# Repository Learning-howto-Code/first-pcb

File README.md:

# first-pcb
I created this project in order to learn how to use Kicad and how the procces works. Hopefully in the future I can create more complicated designs. By the way the github file upload got a little messed up. If there are duplciates of any file, please look at the most recent one, thanks(I'm used to using hte CLI, but didn't want to screw anything up). Also the banner for on blueprint is outdated, but I forgot to chagne it. Sorry

## 3D view

## Schematic 

## Cart Screenshot

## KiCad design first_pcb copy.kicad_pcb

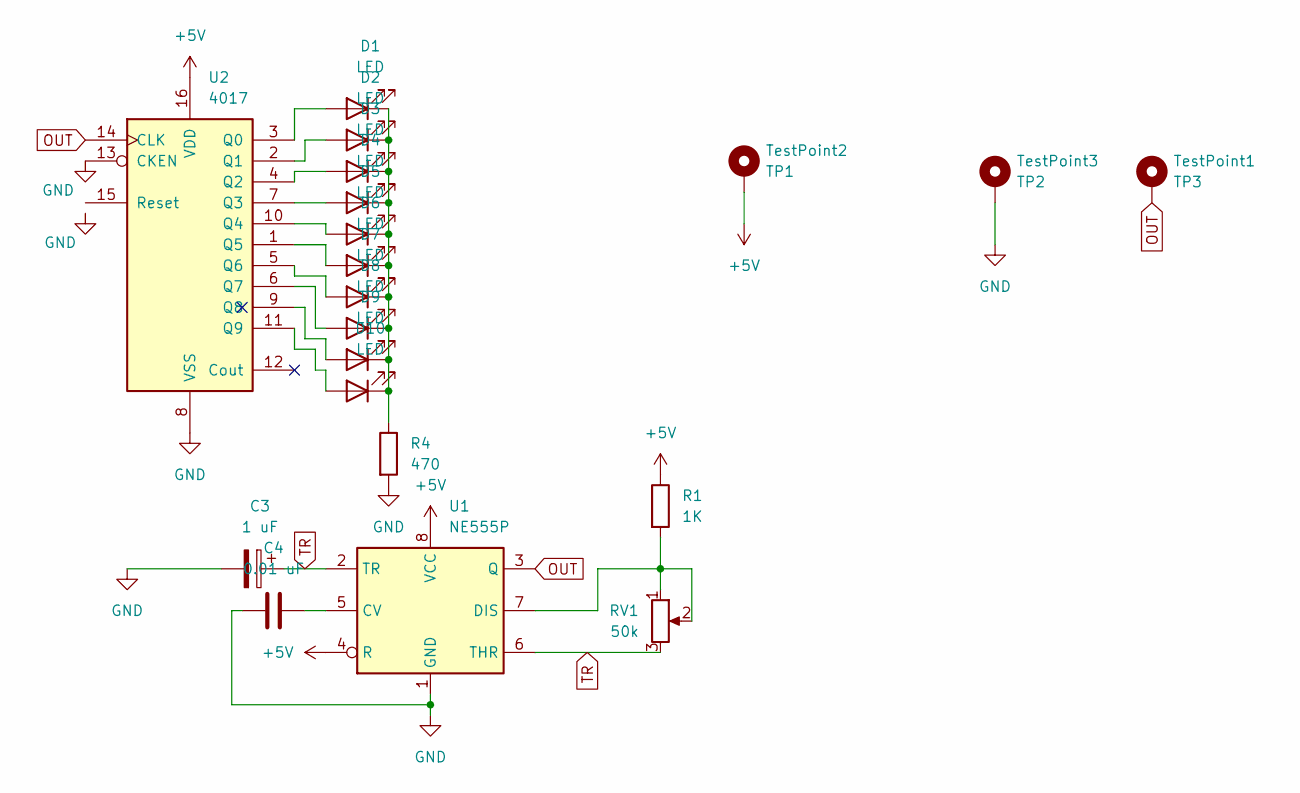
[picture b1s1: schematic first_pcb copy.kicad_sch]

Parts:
C3: 1 uF; CP_Radial_D5.0mm_P2.00mm
C4: 0.01 uF; CP_Radial_D5.0mm_P2.00mm
D1, D2, D3, D4, D5, D6, D7, D8, D9, D10: LED; LED_D3.0mm
R1: 1K; R_Axial_DIN0207_L6.3mm_D2.5mm_P7.62mm_Horizontal
R4: 470; R_Axial_DIN0207_L6.3mm_D2.5mm_P7.62mm_Horizontal
RV1: 50k; Potentiometer_ACP_CA6-H2,5_Horizontal
TestPoint1: TP3; PinSocket_1x01_P2.54mm_Vertical
TestPoint2: TP1; PinSocket_1x01_P2.54mm_Vertical
TestPoint3: TP2; PinSocket_1x01_P2.54mm_Vertical
U1: NE555P; DIP-8_W7.62mm
U2: 4017; N16

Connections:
+5V: R1.1, TestPoint2.1, U1.4 (R), U1.8 (VCC), U2.16 (VDD)
GND: C3.2, C4.1, R4.2, TestPoint3.1, U1.1 (GND), U2.8 (VSS), U2.13 (CKEN)
unnamed: D1.2 (A), U2.3 (Q0)
unnamed: D1.1 (K), D2.1 (K), D3.1 (K), D4.1 (K), D5.1 (K), D6.1 (K), D7.1 (K), D8.1 (K), D9.1 (K), D10.1 (K), R4.1
unnamed: D2.2 (A), U2.2 (Q1)
unnamed: D3.2 (A), U2.4 (Q2)
unnamed: D4.2 (A), U2.7 (Q3)
unnamed: D5.2 (A), U2.10 (Q4)
unnamed: D6.2 (A), U2.1 (Q5)
unnamed: D7.2 (A), U2.5 (Q6)
unnamed: D8.2 (A), U2.6 (Q7)
unnamed: D9.2 (A), U2.9 (Q8)
unnamed: D10.2 (A), U2.11 (Q9)
unnamed: C4.2, U1.5 (CV)
unnamed: R1.2, RV1.1, RV1.2, U1.7 (DIS)
OUT: TestPoint1.1, U1.3 (Q), U2.14 (CLK)
TR: C3.1, RV1.3, U1.2 (TR), U1.6 (THR)

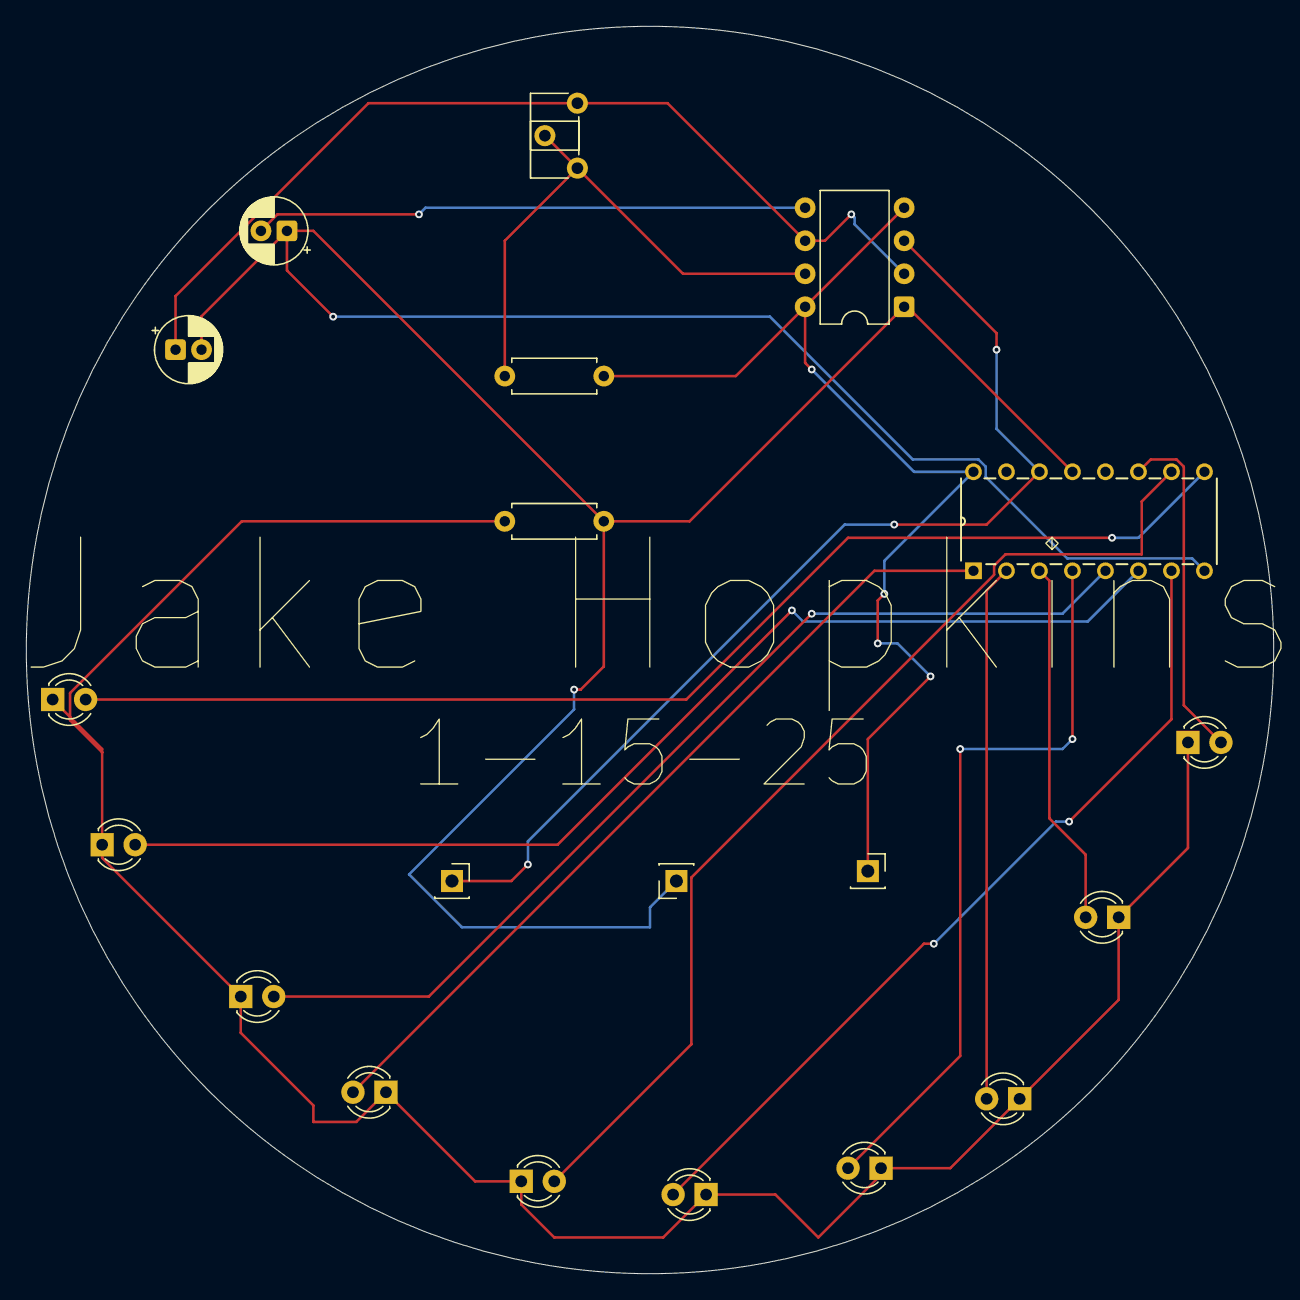
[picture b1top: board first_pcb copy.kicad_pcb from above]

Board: 2 copper layers, 96.0 x 96.0 mm, 20 parts (0 on the bottom side), 17 nets.

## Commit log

2026-01-07 Added kicad files
2026-01-07 added image
2026-01-07 added cart screenshot
2026-01-10 updated files
2026-01-10 uopdated img
2026-01-10 added note
2026-01-11 added schematic
2026-01-16 updated cart
2026-01-16 added more files
